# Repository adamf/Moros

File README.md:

Moros
=====

Moros is an Arduino-based game clock.

This project provides all the components needed to build the case, electronics
and software for a game clock. 

Features
--------
* Large, easy to read numbers
* Graphical display of flag (currently the flag of the USSR)
* Durable arcade buttons for clock buttons
* Extensible & open design, including the case, electronics and software (MIT License)
* Built by avid blitz chess players

Software
========

The Moros software is written in C++ for the Arduino microcontroller platform. The software
was built for the Arduino Uno and Arduino Micro. The software was built and tested on Ubuntu 14.04,
but should build for any platform with small changes to the Makefile.

For Ubuntu 14.04, the packages required can be installed with:

    sudo apt-get update && apt-get install arduino arduino-code arduino-mk

And then to build & install on the microcontroller:

    cd moros
    make upload

We also provide serial port debug output (this starts screen(1), quit with ctrl-a k):

    make upload monitor

Case
====

The case model is built with OpenSCAD, then exported into SketchUp for splitting into 3D-printable format.

Shield
======

See the README.md file in the shield/ directory in this repository.

TODO
====
* Support displaying hours
* Re-add displaying 10th of a second
* Update case to reflect use of arcade-style buttons
* Update case to reflect the reset button
* Update shield to reflect reset button to ground, not VCC
* Clean up case SCAD code, and add README and Makefile for generation of 3D-printable models
* Support saving the time between reboots

Copyright 2014 Adam Fletcher and Matt Zimmerman

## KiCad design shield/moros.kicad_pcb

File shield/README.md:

Moros Arduino Micro Shield
==========================

This is the [KiCad](http://www.kicad-pcb.org) project for the Arduino Micro
shield used to build the Moros chess clock. This shield makes it much easier
to attach the OLED screens and buttons to the Arduino in a compact format
suitable for shoving inside the Moros case.

To use this project you need the latest version of KiCad, or a version
built from head after December 28th, 2014. In Ubuntu it is easiest to add
the [KiCad PPA](https://code.launchpad.net/~js-reynaud/+archive/ubuntu/ppa-kicad) and
install KiCad from there. You'll need to set the KIGITHUB environment variable:

    export KIGITHUB='https://github.com/kicad'

Otherwise KiCad won't find its component libraries.

Three other component libraries are required for this project, from two different repositories:

* ab2_header and ab2_idc from [AB2's KiCad Library set](https://github.com/ab2tech/KiCad)
* arduino_micro_shield from [Adam Fletcher's Arduino Micro Shield Component & Footprint](https://github.com/adamf/arduino_micro_shield)

Both are included in this source tree for convenience. 

Opening the moros.pro file in KiCad will load all needed files. From there the schematic can be edited, 
a netlist generated, and a PCB laid out. The PCB in this repo is suitable for export to Gerber format files.
In order to send those Gerber format files to the preferred fab, [OSH Park](http://oshpark.com), the Gerber
files output by KiCad must be renamed:

    cd gerber
    bash rename_and_zip.sh

The resulting .zip file can be uploaded to OSH Park for fabrication.

Copyright 2014 Adam Fletcher and Matt Zimmerman

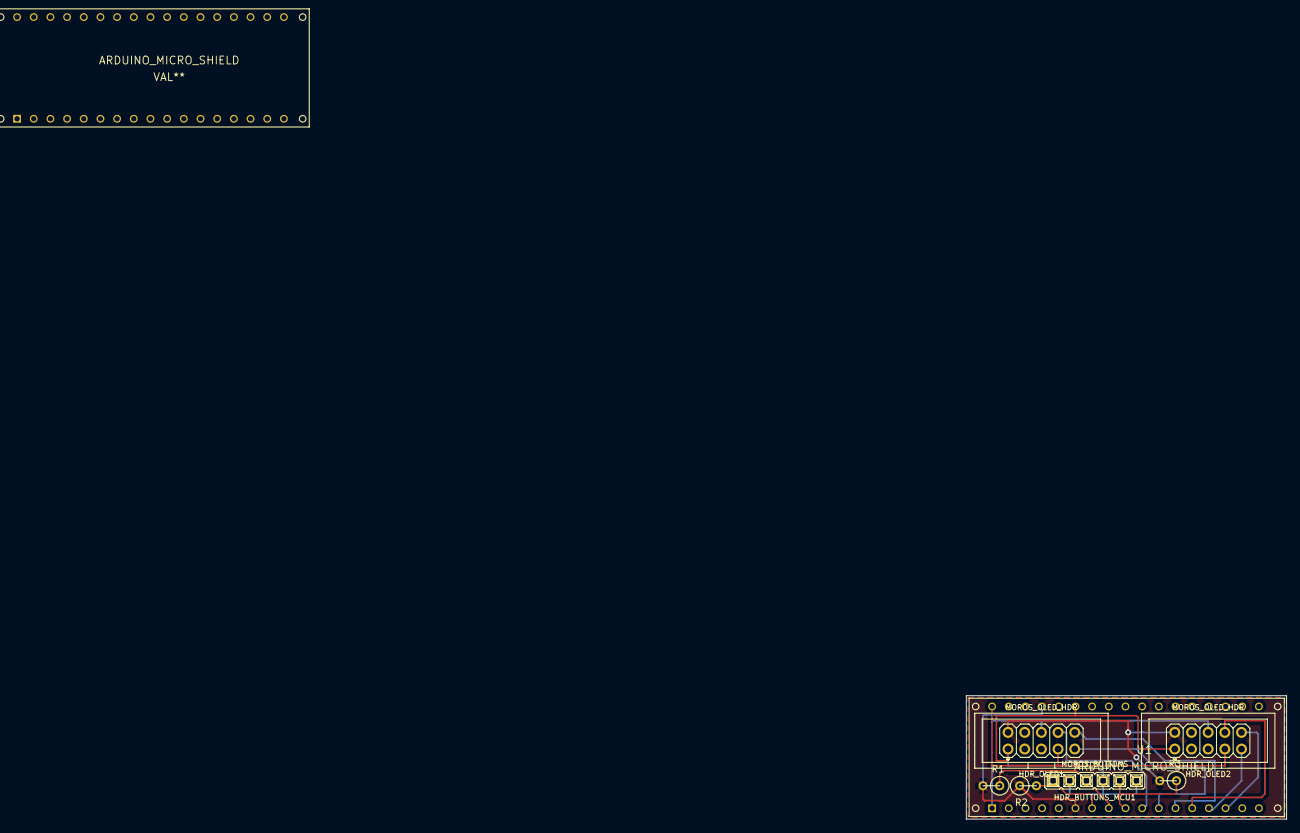
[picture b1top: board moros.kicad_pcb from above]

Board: 2 copper layers, 48.8 x 18.8 mm, 8 parts (0 on the bottom side), 13 nets.

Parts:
ARDUINO_MICRO_SHIELD: VAL**; ARDUINO_MICRO_SHIELD
HDR_BUTTONS_MCU1: MOROS_BUTTONS; AB2_HDR_F06-1V
HDR_OLED1, HDR_OLED2: MOROS_OLED_HDR; AB2_HDR_M05-2V-S
R1, R2, R3: 10k; R1
U1: ARDUINO_MICRO_SHIELD

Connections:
+5V: HDR_BUTTONS_MCU1.2, HDR_BUTTONS_MCU1.4, HDR_BUTTONS_MCU1.6, HDR_OLED1.1, HDR_OLED2.1, U1.5V
/ToCS1: HDR_OLED1.8, U1.5
/ToCS2: HDR_OLED2.8, U1.8
/ToDC1: HDR_OLED1.9, U1.6
/ToDC2: HDR_OLED2.9, U1.9
/ToMOSI: HDR_OLED1.6, HDR_OLED2.6, U1.MO
/ToPly1Btn: HDR_BUTTONS_MCU1.1, R2.2, U1.2
/ToPly2Btn: HDR_BUTTONS_MCU1.3, R1.1, U1.3
/ToRST1: HDR_OLED1.10, U1.7
/ToRST2: HDR_OLED2.10, U1.10
/ToRstBtn: HDR_BUTTONS_MCU1.5, R3.1, U1.4
/ToSCK: HDR_OLED1.7, HDR_OLED2.7, U1.SCK
GND: HDR_OLED1.2, HDR_OLED2.2, R1.2, R2.1, R3.2, U1.GND

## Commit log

2014-08-15 Fix flag state problems
2014-08-15 Rotate case for better printing
2014-08-15 Update copyright
2014-08-18 Add Makefile for use with arduino-mk
2014-08-18 I FEEL THE NEED FOR SPEED. Use 115200bps
2014-08-18 Rmeove dead code
2014-08-18 Factor out handle_button_press()
2014-08-18 Remove more dead code
2014-08-18 Remove yet more dead code
2014-08-18 5 second timer
2014-08-18 Infer length of array rather than having a #define
2014-08-18 115200 serial monitor at runtime too, whee
2014-08-18 s/CLOCK_STOP/NONE/g
2014-08-18 Ignore build-* directories (used by arduino-mk)
2014-08-18 Break out buttons into an array, clear warnings
2014-08-18 Declare screens as an array rather than #defines
2014-08-18 Use C99 initializers all around
2014-08-18 Fix button mapping
2014-08-18 Refactor display logic
2014-08-18 Yummy comments
2014-08-18 Add fucking printf
2014-08-18 Add printf implementation
2014-08-18 Move TODO to the top where it belongs
2014-08-18 Rename function
2014-08-18 Remove debug
2014-08-18 Refactor main loop
2014-08-18 Remove dead code
2014-08-18 Remove dead comment
2014-08-18 Factor out TFT stuff into Screen
2014-08-18 Initialize tft to NULL
2014-08-18 player -> Player
2014-08-18 Update comments
2014-08-18 Factor out Clock and fix lurking integer overflow bug
2014-08-18 Make Screen a class
2014-08-18 Move display logic into Screen
2014-08-18 Don't draw all the text twice
2014-08-18 Initialize prev_text
2014-08-18 Factor out clock logic into a class
2014-08-18 Convert Player to a class, move its logic there
2014-08-18 Declare screens in player init instead of having a static array
2014-08-18 Partial refactoring of button into a class
2014-08-18 Factor more of button
2014-08-18 Move font #defines into Screen
    These really should be constants or something
2014-08-18 Controller class
2014-08-18 Move button handler into controller
2014-08-18 Remove unnecessary #define
2014-08-18 Make button interrupt handling a bit less crappy
2014-08-18 Comment and format main loop logic to be readable
2014-08-18 Move interrupt handlers more into the controller rather than Button
2014-08-18 Comment
2014-08-18 Remove extraneous test
2014-08-18 Fix indent
2014-09-09 Add support for oled, and time formatting
2014-09-10 fix interrupt pins issue
2014-09-10 Add U8glib
2014-09-10 Fix formatting of tenths
2014-09-10 Add time formatting function and fonts
2014-09-10 Add red flag
2014-09-10 Move flag logic into controller
2014-09-10 Once flag has fallen, end the game
2014-09-14 Move TFT-specific code to a header
2014-10-03 -std=c++11
2014-10-03 Stub reset/power button logic
    - Add PollButton class based on digitalRead
    - Expect a button on pin A0
    - When it's held down for 3 seconds, we'll reset
    - When it's held down for 5 seconds, we'll power off
2014-10-03 Update TODO
2014-10-03 Implement reset
2014-10-03 Initial attempt to power off (doesn't work yet)
2014-12-02 Working OLED
2014-12-16 Better font support
2014-12-22 First board
2014-12-23 Clean up edges, prep files for OSHpark fab
2014-12-23 Demo schematic
2014-12-30 change location of micro component library
2014-12-30 Fix reset button's use of the internal AVR pull-up resistor
2014-12-30 Implement pause, stub out time setting
2014-12-30 Add flag
2014-12-30 Make reset clear the flag image
2014-12-30 Add makefile rule for flag image header generation
2014-12-30 Update todo list
2014-12-30 Get relative path for schematic component libraries working, and move libraries into source tree
2014-12-30 A few more relative paths, fix reference to component
2014-12-30 last path fix
2014-12-30 remove unused submodule
2014-12-30 update to latest version of micro shield
2014-12-30 Add README
2014-12-30 fix readme code block
2014-12-30 Fix links
2014-12-30 Add more information to README
2014-12-30 fix code blocks
2014-12-30 Re-fix code block
2014-12-30 Automatically install FTOLED
2014-12-31 Fix board reference and monitor baud rate
2014-12-31 Remove debugging background colors
2015-01-01 Refactor main tick loop into state machine.
2015-01-01 Add notion of just released to mode button
2015-01-01 Start of mode button handling refactor
2015-01-01 setting and blinking
2015-01-01 Clock setting works
2015-01-01 Add state diagram
2015-01-01 Update TODOs
2015-01-03 Remove unused includes and screen consts
2015-01-03 Update todo, first try at not leaving the screen blank on time setting screen change
2015-01-04 Fix letter P in CCCP in flag
2015-01-10 Fix syntax error in footprint library file
2015-01-10 Use new arduino shield template
2015-01-19 Un-break the build
2015-01-19 Blink me harder
2015-01-19 Adjust reset button timeouts
2015-02-06 Update case with thicker walls, usb port, reset button port, code refactor
2015-02-06 Add new sketchup version of the case
